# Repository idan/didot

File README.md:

# Didot

A fully-wireless split keyboard. 6×4+5 column-staggered, with a rotary encoder.

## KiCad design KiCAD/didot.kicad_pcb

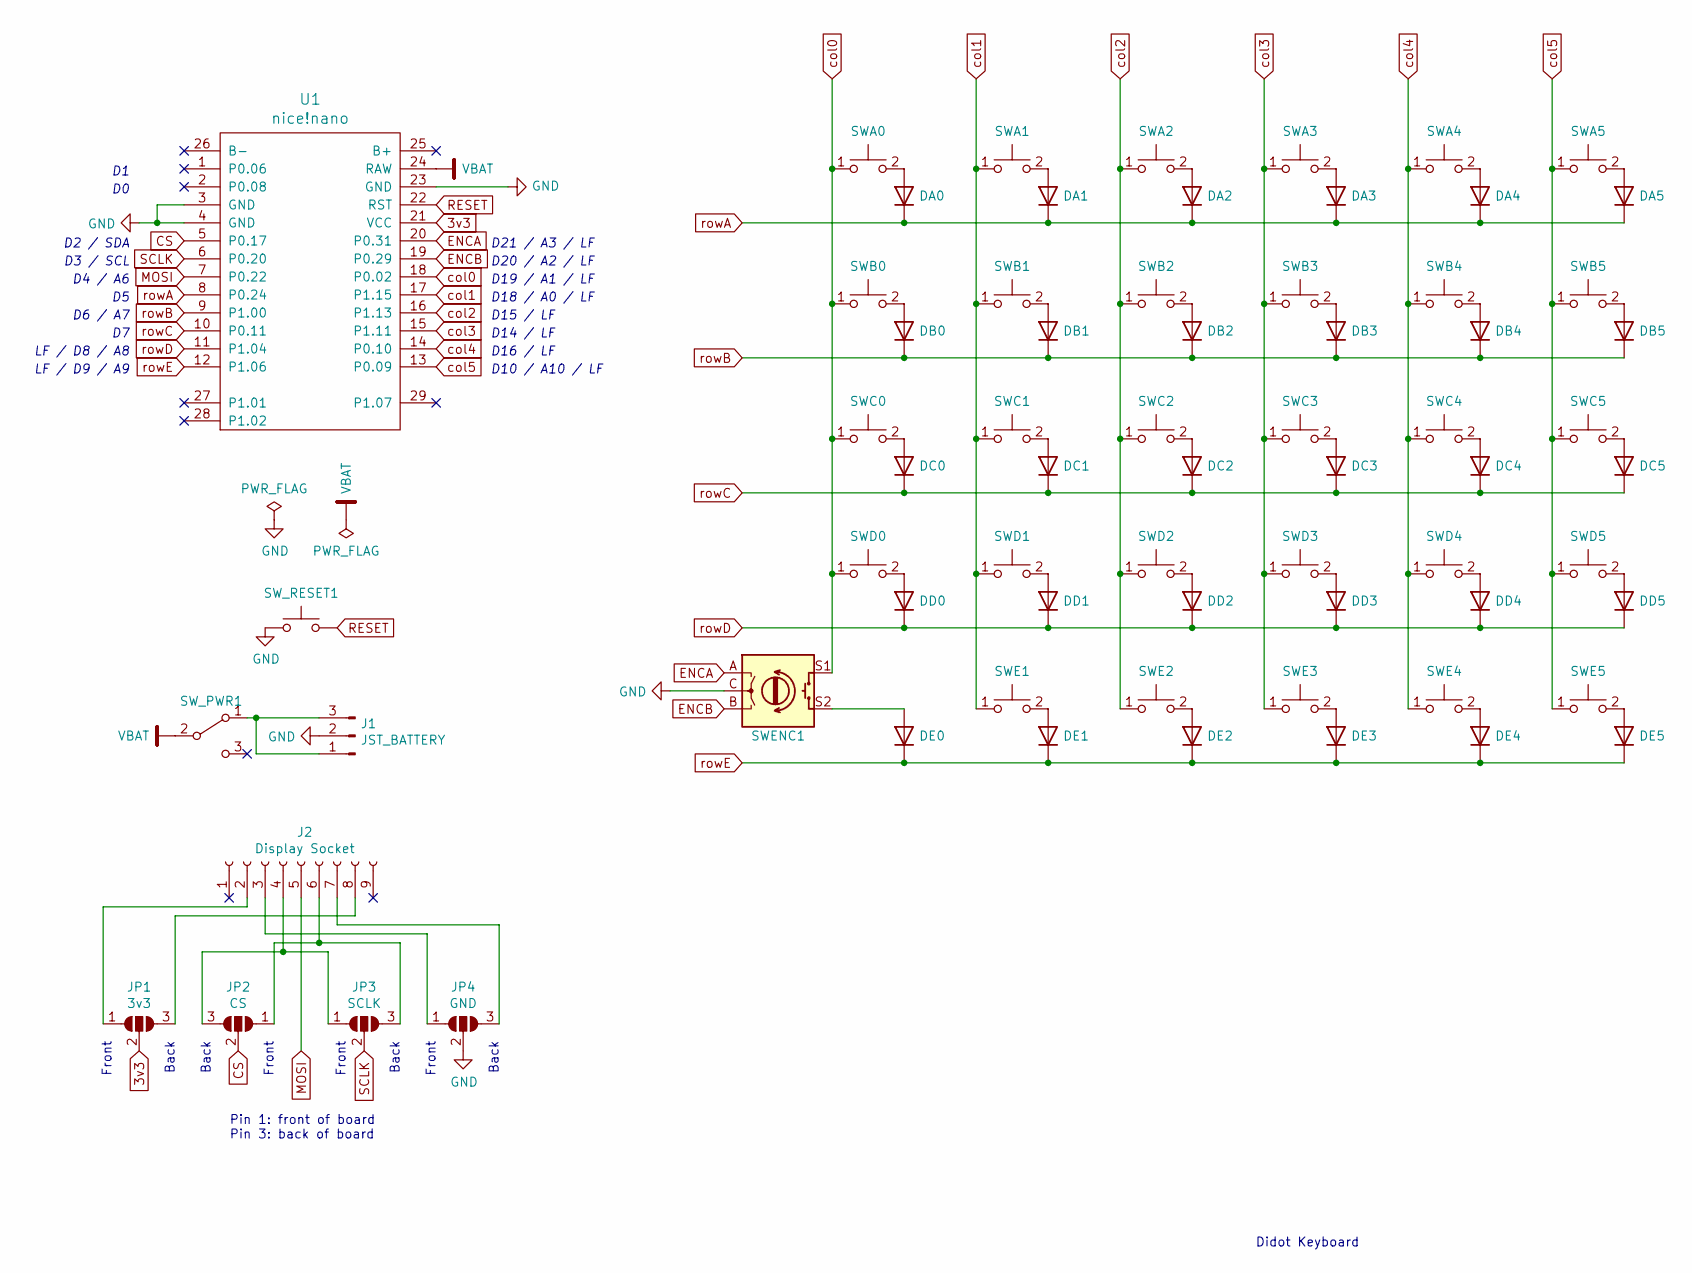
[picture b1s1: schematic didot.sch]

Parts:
DA0, DA1, DA2, DA3, DA4, DA5: 1N4148W; Diode_SOD123
DB0, DB1, DB2, DB3, DB4, DB5: 1N4148W; Diode_SOD123
DC0, DC1, DC2, DC3, DC4, DC5: 1N4148W; Diode_SOD123
DD0, DD1, DD2, DD3, DD4, DD5: 1N4148W; Diode_SOD123
DE0, DE1, DE2, DE3, DE4, DE5: 1N4148W; Diode_SOD123
J1: JST_BATTERY; JST_PH_S3B-PH-K_1x03_P2.00mm_Horizontal
J2: Display Socket; 1X09_ROUND_70
JP1: 3v3; ReversibleDisplayJumper
JP2: CS; ReversibleDisplayJumper
JP3: SCLK; ReversibleDisplayJumper
JP4: GND; ReversibleDisplayJumper
SWA0, SWA1, SWA2, SWA3, SWA4, SWA5: SW_KEY; Kailh_socket_PG1350_optional_reversible
SWB0, SWB1, SWB2, SWB3, SWB4, SWB5: SW_KEY; Kailh_socket_PG1350_optional_reversible
SWC0, SWC1, SWC2, SWC3, SWC4, SWC5: SW_KEY; Kailh_socket_PG1350_optional_reversible
SWD0, SWD1, SWD2, SWD3, SWD4, SWD5: SW_KEY; Kailh_socket_PG1350_optional_reversible
SWE1, SWE2: SW_KEY; Kailh_socket_PG1350_optional_reversible_1.5u
SWE3, SWE4, SWE5: SW_KEY; Kailh_socket_PG1350_optional_reversible
SWENC1: Rotary_Encoder_Switch; RotaryEncoder_Alps_EC11E-Switch_Vertical_H20mm-keebio_modif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
SW_PWR1: SW_SPDT; SW_Slide_1P2T_CK_OS102011MS2Q
SW_RESET1: SW_Push; TACT_SWITCH_TVBP06
U1: nice!nano; ProMicro

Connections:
3v3: JP1.2 (C), U1.21 (VCC)
CS: JP2.2 (C), U1.5 (P0.17)
ENCA: SWENC1.A, U1.20 (P0.31)
ENCB: SWENC1.B, U1.19 (P0.29)
GND: J1.2, JP4.2 (C), SWENC1.C, SW_RESET1.1, U1.3 (GND), U1.4 (GND), U1.23 (GND)
MOSI: J2.5, U1.7 (P0.22)
unnamed: DA0.2 (A), SWA0.2
unnamed: DA1.2 (A), SWA1.2
unnamed: DA2.2 (A), SWA2.2
unnamed: DA3.2 (A), SWA3.2
unnamed: DA4.2 (A), SWA4.2
unnamed: DA5.2 (A), SWA5.2
unnamed: DB0.2 (A), SWB0.2
unnamed: DB1.2 (A), SWB1.2
unnamed: DB2.2 (A), SWB2.2
unnamed: DB3.2 (A), SWB3.2
unnamed: DB4.2 (A), SWB4.2
unnamed: DB5.2 (A), SWB5.2
unnamed: DC0.2 (A), SWC0.2
unnamed: DC1.2 (A), SWC1.2
unnamed: DC2.2 (A), SWC2.2
unnamed: DC3.2 (A), SWC3.2
unnamed: DC4.2 (A), SWC4.2
unnamed: DC5.2 (A), SWC5.2
unnamed: DD0.2 (A), SWD0.2
unnamed: DD1.2 (A), SWD1.2
unnamed: DD2.2 (A), SWD2.2
unnamed: DD3.2 (A), SWD3.2
unnamed: DD4.2 (A), SWD4.2
unnamed: DD5.2 (A), SWD5.2
unnamed: DE0.2 (A), SWENC1.S2
unnamed: DE1.2 (A), SWE1.2
unnamed: DE2.2 (A), SWE2.2
unnamed: DE3.2 (A), SWE3.2
unnamed: DE4.2 (A), SWE4.2
unnamed: DE5.2 (A), SWE5.2
unnamed: J1.1, J1.3, SW_PWR1.1 (A)
unnamed: J2.2, JP1.1 (A)
unnamed: J2.3, JP4.1 (A)
unnamed: J2.4, JP2.3 (B), JP3.1 (A)
unnamed: J2.6, JP2.1 (A), JP3.3 (B)
unnamed: J2.7, JP4.3 (B)
unnamed: J2.8, JP1.3 (B)
RESET: SW_RESET1.2, U1.22 (RST)
SCLK: JP3.2 (C), U1.6 (P0.20)
VBAT: SW_PWR1.2 (B), U1.24 (RAW)
col0: SWA0.1, SWB0.1, SWC0.1, SWD0.1, SWENC1.S1, U1.18 (P0.02)
col1: SWA1.1, SWB1.1, SWC1.1, SWD1.1, SWE1.1, U1.17 (P1.15)
col2: SWA2.1, SWB2.1, SWC2.1, SWD2.1, SWE2.1, U1.16 (P1.13)
col3: SWA3.1, SWB3.1, SWC3.1, SWD3.1, SWE3.1, U1.15 (P1.11)
col4: SWA4.1, SWB4.1, SWC4.1, SWD4.1, SWE4.1, U1.14 (P0.10)
col5: SWA5.1, SWB5.1, SWC5.1, SWD5.1, SWE5.1, U1.13 (P0.09)
rowA: DA0.1 (K), DA1.1 (K), DA2.1 (K), DA3.1 (K), DA4.1 (K), DA5.1 (K), U1.8 (P0.24)
rowB: DB0.1 (K), DB1.1 (K), DB2.1 (K), DB3.1 (K), DB4.1 (K), DB5.1 (K), U1.9 (P1.00)
rowC: DC0.1 (K), DC1.1 (K), DC2.1 (K), DC3.1 (K), DC4.1 (K), DC5.1 (K), U1.10 (P0.11)
rowD: DD0.1 (K), DD1.1 (K), DD2.1 (K), DD3.1 (K), DD4.1 (K), DD5.1 (K), U1.11 (P1.04)
rowE: DE0.1 (K), DE1.1 (K), DE2.1 (K), DE3.1 (K), DE4.1 (K), DE5.1 (K), U1.12 (P1.06)

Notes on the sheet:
Didot Keyboard
D10 / A10 / LF
D16 / LF
D14 / LF
D15 / LF
D18 / A0 / LF
D19 / A1 / LF
D20 / A2 / LF
D21 / A3 / LF
LF / D9 / A9
LF / D8 / A8
D6 / A7
D4 / A6
D3 / SCL
D2 / SDA
Pin 1: front of board Pin 3: back of board
Front
Back

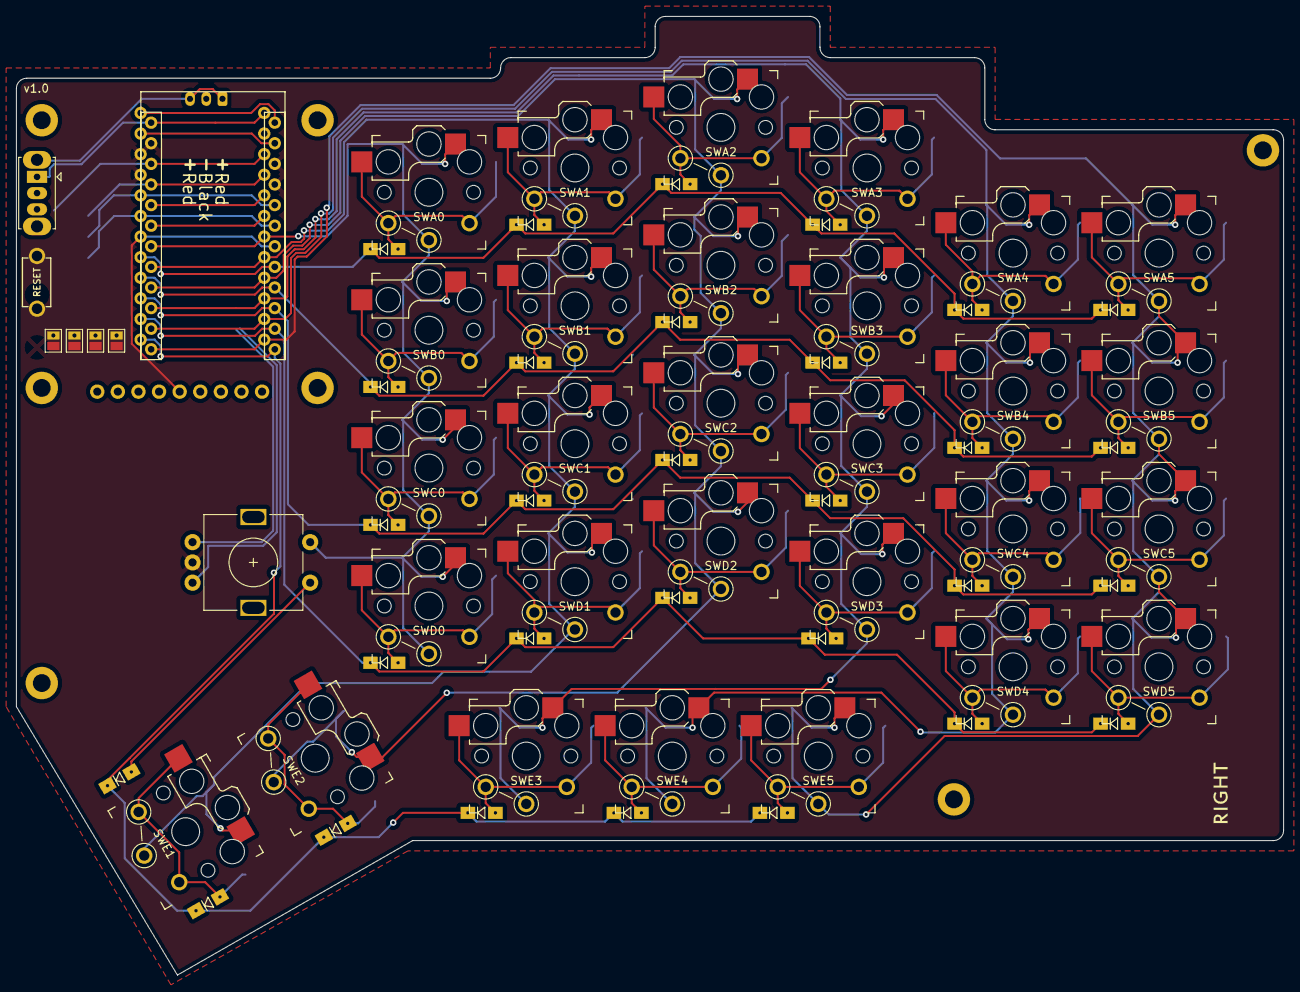
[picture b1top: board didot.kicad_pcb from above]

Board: 2 copper layers, 156.2 x 118.2 mm, 77 parts (1 on the bottom side), 57 nets.

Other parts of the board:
Ref**: Val**; didot_right
TH1, TH1#2, TH1#3, TH1#4, TH1#5, TH1#6, TH1#7: HOLE; M2_HOLE_PCB

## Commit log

2021-01-24 Add footprints / pretty library
2021-01-24 enlarge board outline
2021-01-24 Finish rewiring of keys
2021-01-25 Add waveshare display footprint
2021-01-25 Use waveshare display footprint
2021-02-28 Clean up routing, add JST pin markings
2021-08-14 Complete v1.0 layout with footprints
2021-08-14 Organize project layout
2021-08-14 Add "other" directory
2021-08-14 Move display to align with corner screw
2021-08-14 Fix small ground pour issues
2021-08-14 Adjust copper fill layers
2021-08-14 Add images
2021-08-14 Add basic README
2021-08-14 Fix readme image embeds
2021-08-15 Derp, fix path case in readme
2022-04-01 Whatever was on my PC
